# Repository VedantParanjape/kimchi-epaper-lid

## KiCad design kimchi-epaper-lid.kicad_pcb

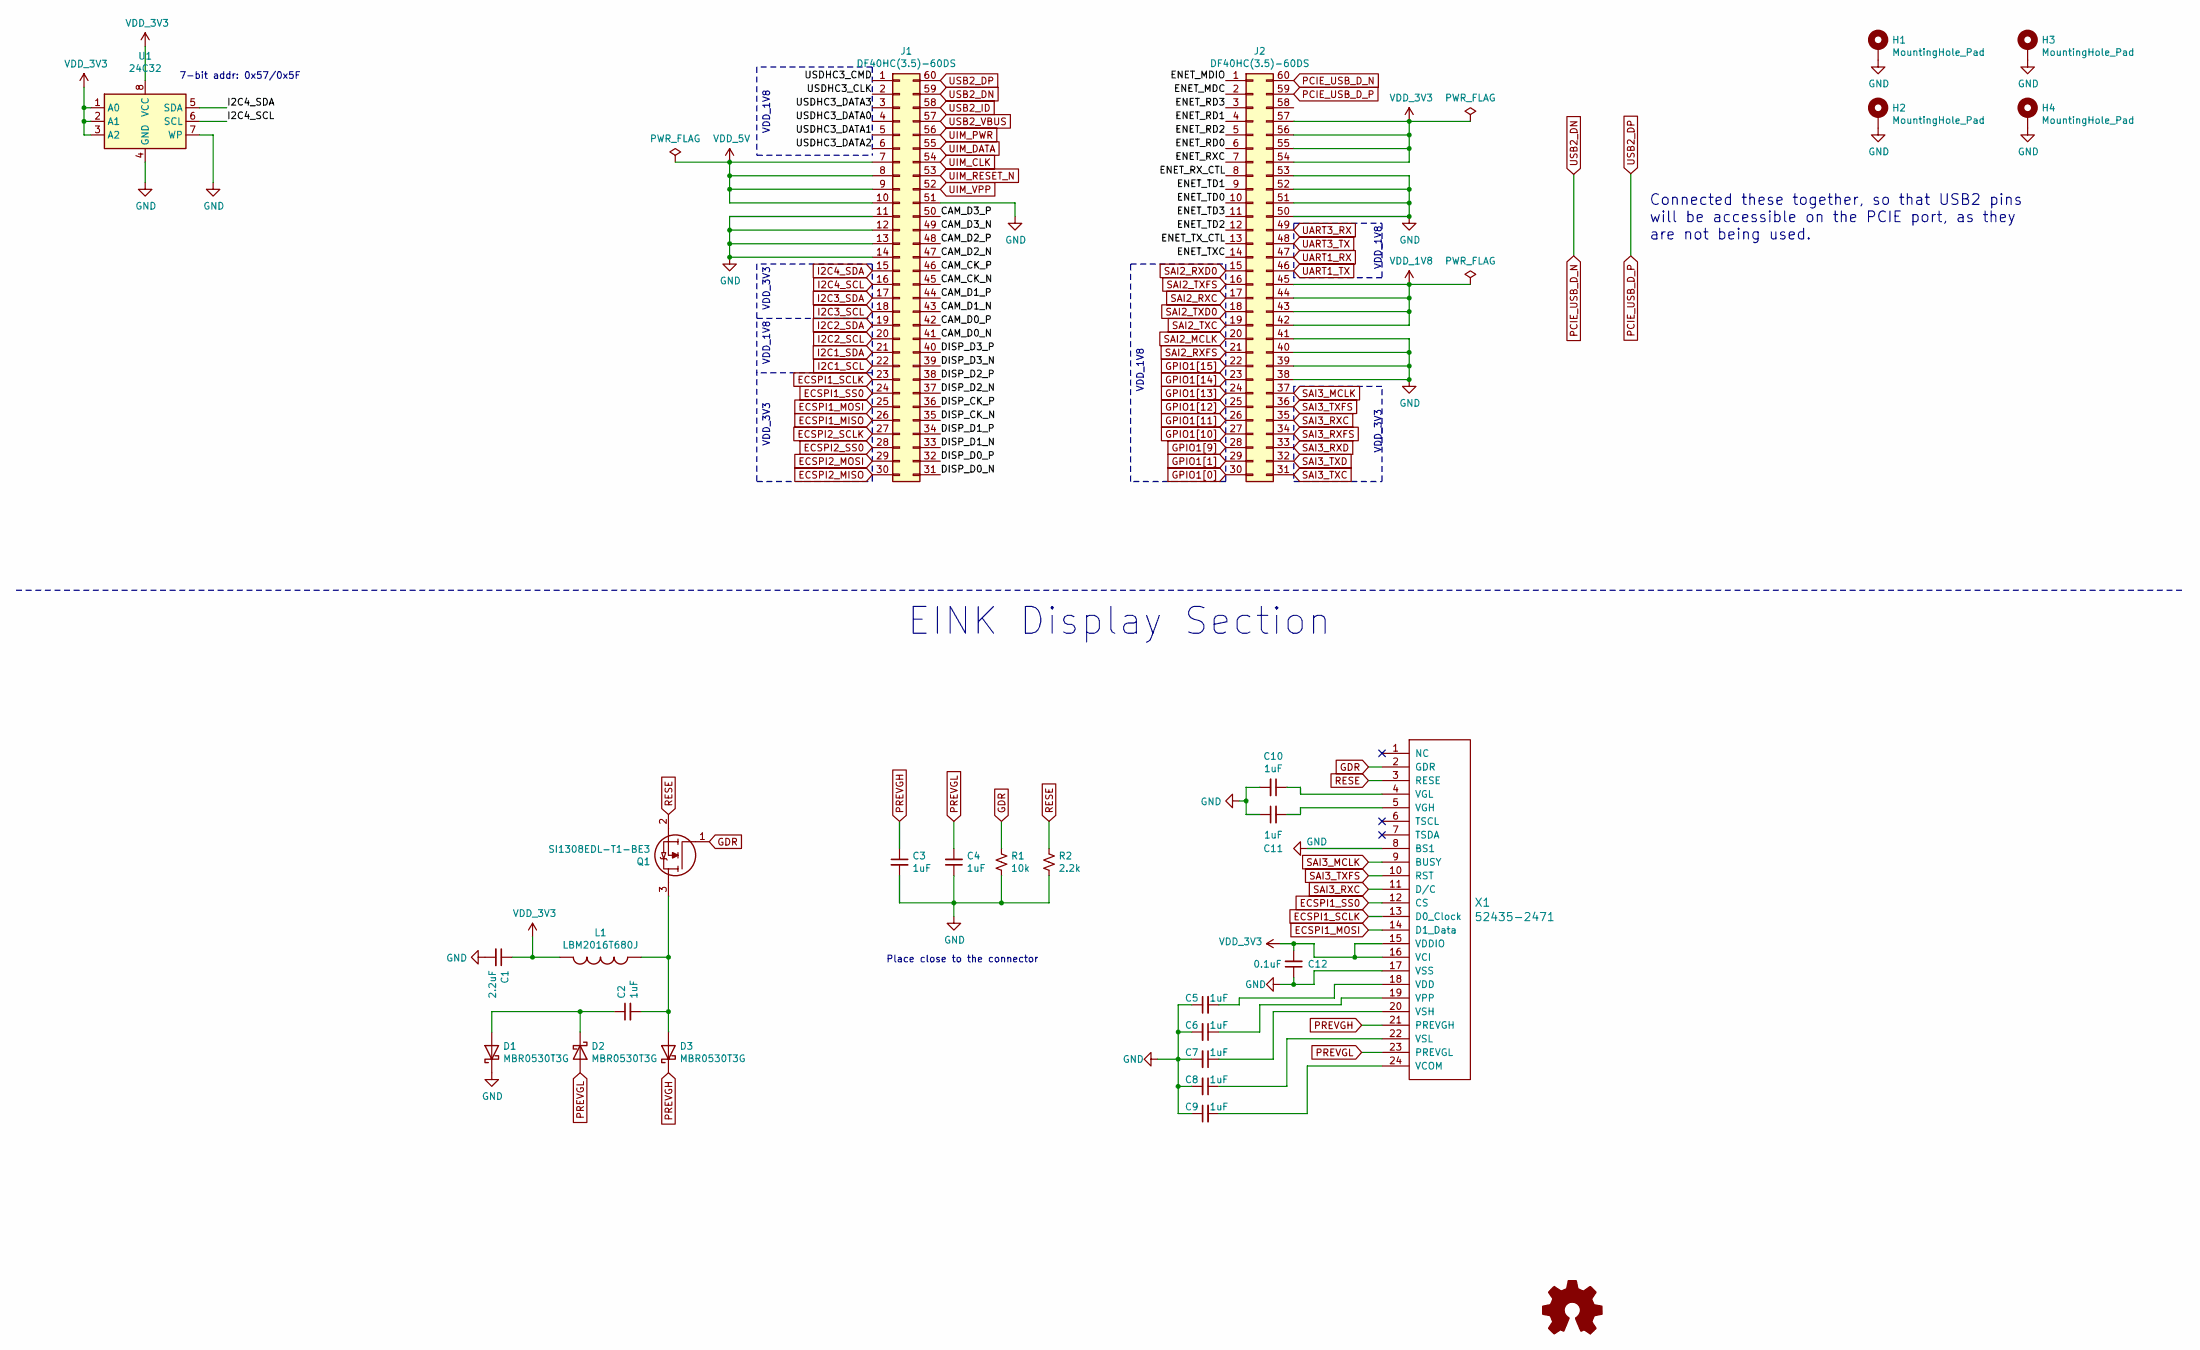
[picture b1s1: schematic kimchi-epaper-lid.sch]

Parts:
C1: 2.2uF; C_0603_1608Metric
C2, C3, C4, C5, C6, C7, C8, C9, C10, C11: 1uF; C_0603_1608Metric
C12: 0.1uF; C_0603_1608Metric
D1, D2, D3: MBR0530T3G; D_SOD-123
H1, H2, H3, H4: MountingHole_Pad; MountingHole_3mm_Pad
J1, J2: DF40HC(3.5)-60DS
L1: LBM2016T680J; INDC2016X180N
LOGO1: Logo_Open_Hardware_Small; OSHW-Logo_5.7x6mm_SilkScreen
Q1: SI1308EDL-T1-BE3; SOT65P210X110-3N; Manufacturer_Part_Number SI1308EDL-T1-BE3; Mouser Part Number 78-SI1308EDL-T1-BE3
R1: 10k; R_0603_1608Metric
R2: 2.2k; R_0603_1608Metric
U1: 24C32; DFN-8-1EP_3x2mm_P0.5mm_EP1.36x1.46mm; Part M24C32-FMC6TG
X1: 52435-2471; MOLEX_52435-2471

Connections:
/CAM_CK_N: J1.45
/CAM_CK_P: J1.46
/CAM_D0_N: J1.41
/CAM_D0_P: J1.42
/CAM_D1_N: J1.43
/CAM_D1_P: J1.44
/CAM_D2_N: J1.47
/CAM_D2_P: J1.48
/CAM_D3_N: J1.49
/CAM_D3_P: J1.50
/DISP_CK_N: J1.35
/DISP_CK_P: J1.36
/DISP_D0_N: J1.31
/DISP_D0_P: J1.32
/DISP_D1_N: J1.33
/DISP_D1_P: J1.34
/DISP_D2_N: J1.37
/DISP_D2_P: J1.38
/DISP_D3_N: J1.39
/DISP_D3_P: J1.40
/ENET_MDC: J2.2
/ENET_MDIO: J2.1
/ENET_RD0: J2.6
/ENET_RD1: J2.4
/ENET_RD2: J2.5
/ENET_RD3: J2.3
/ENET_RXC: J2.7
/ENET_RX_CTL: J2.8
/ENET_TD0: J2.10
/ENET_TD1: J2.9
/ENET_TD2: J2.12
/ENET_TD3: J2.11
/ENET_TXC: J2.14
/ENET_TX_CTL: J2.13
/USDHC3_CLK: J1.2
/USDHC3_CMD: J1.1
/USDHC3_DATA0: J1.4
/USDHC3_DATA1: J1.5
/USDHC3_DATA2: J1.6
/USDHC3_DATA3: J1.3
ECSPI1_MISO: J1.26
ECSPI1_MOSI: J1.25, X1.14 (D1_Data)
ECSPI1_SCLK: J1.23, X1.13 (D0_Clock)
ECSPI1_SS0: J1.24, X1.12 (CS)
ECSPI2_MISO: J1.30
ECSPI2_MOSI: J1.29
ECSPI2_SCLK: J1.27
ECSPI2_SS0: J1.28
GDR: Q1.1, R1.1, X1.2 (GDR)
GND: C1.2, C3.2, C4.1, C5.1, C6.2, C7.2, C8.2, C9.1, C10.2, C11.1, C12.1, D1.1 (K), H1.1, H2.1, H3.1, H4.1, J1.11, J1.12, J1.13, J1.14, J1.51, J2.38, J2.39, J2.40, J2.41, J2.50, J2.51, J2.52, J2.53, R1.2, R2.2, U1.4 (GND), U1.7 (WP), X1.8 (BS1), X1.17 (VSS)
GPIO1[0]: J2.30
GPIO1[1]: J2.29
GPIO1[9]: J2.28
GPIO1[10]: J2.27
GPIO1[11]: J2.26
GPIO1[12]: J2.25
GPIO1[13]: J2.24
GPIO1[14]: J2.23
GPIO1[15]: J2.22
I2C1_SCL: J1.22
I2C1_SDA: J1.21
I2C2_SCL: J1.20
I2C2_SDA: J1.19
I2C3_SCL: J1.18
I2C3_SDA: J1.17
I2C4_SCL: J1.16, U1.6 (SCL)
I2C4_SDA: J1.15, U1.5 (SDA)
unnamed: C2.1, D1.2 (A), D2.1 (K)
unnamed: C2.2, D3.2 (A), L1.2, Q1.3
unnamed: C5.2, X1.18 (VDD)
unnamed: C6.1, X1.19 (VPP)
unnamed: C7.1, X1.20 (VSH)
unnamed: C8.1, X1.22 (VSL)
unnamed: C9.2, X1.24 (VCOM)
unnamed: C10.1, X1.4 (VGL)
unnamed: C11.2, X1.5 (VGH)
PCIE_USB_D_N: J1.59, J2.60
PCIE_USB_D_P: J1.60, J2.59
PREVGH: C3.1, D3.1 (K), X1.21 (PREVGH)
PREVGL: C4.2, D2.2 (A), X1.23 (PREVGL)
RESE: Q1.2, R2.1, X1.3 (RESE)
SAI2_MCLK: J2.20
SAI2_RXC: J2.17
SAI2_RXD0: J2.15
SAI2_RXFS: J2.21
SAI2_TXC: J2.19
SAI2_TXD0: J2.18
SAI2_TXFS: J2.16
SAI3_MCLK: J2.37, X1.9 (BUSY)
SAI3_RXC: J2.35, X1.11 (D/C)
SAI3_RXD: J2.33
SAI3_RXFS: J2.34
SAI3_TXC: J2.31
SAI3_TXD: J2.32
SAI3_TXFS: J2.36, X1.10 (RST)
UART1_RX: J2.47
UART1_TX: J2.46
UART3_RX: J2.49
UART3_TX: J2.48
UIM_CLK: J1.54
UIM_DATA: J1.55
UIM_PWR: J1.56
UIM_RESET_N: J1.53
UIM_VPP: J1.52
USB2_ID: J1.58
USB2_VBUS: J1.57
VDD_1V8: J2.42, J2.43, J2.44, J2.45
VDD_3V3: C1.1, C12.2, J2.54, J2.55, J2.56, J2.57, L1.1, U1.1 (A0), U1.2 (A1), U1.3 (A2), U1.8 (VCC), X1.15 (VDDIO), X1.16 (VCI)
VDD_5V: J1.7, J1.8, J1.9, J1.10

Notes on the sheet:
7-bit addr: 0x57/0x5F
VDD_1V8
VDD_3V3
EINK Display Section
Place close to the connector
Connected these together, so that USB2 pins will be accessible on the PCIE port, as they are not being used.

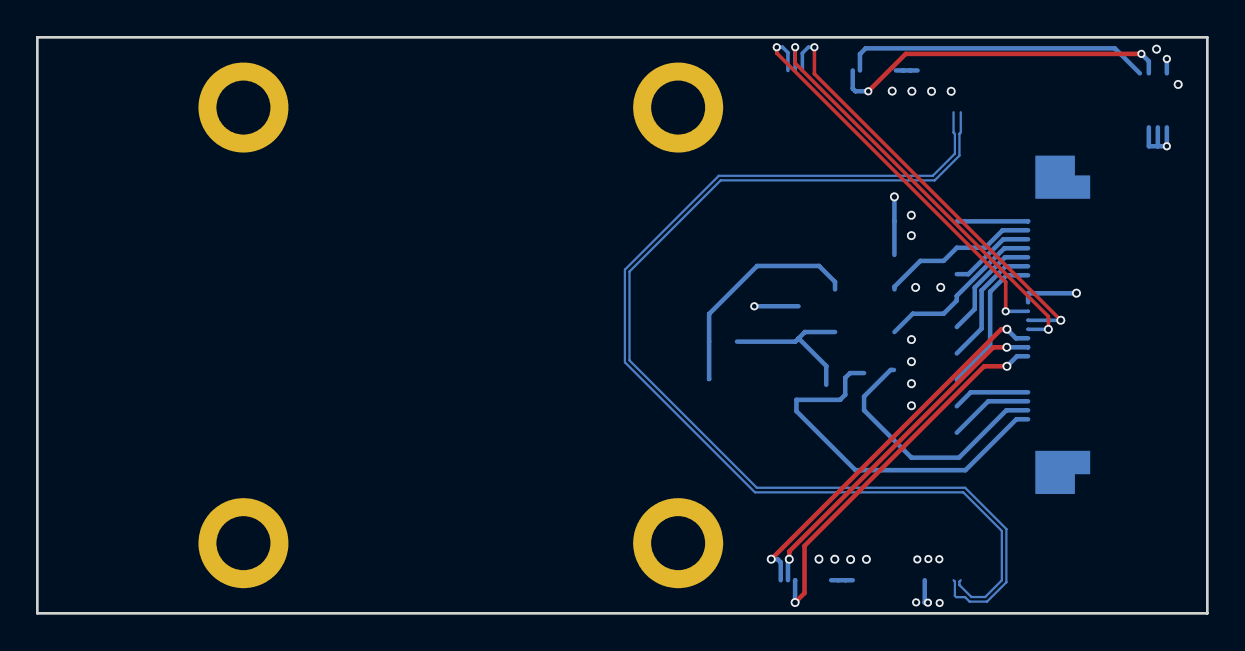
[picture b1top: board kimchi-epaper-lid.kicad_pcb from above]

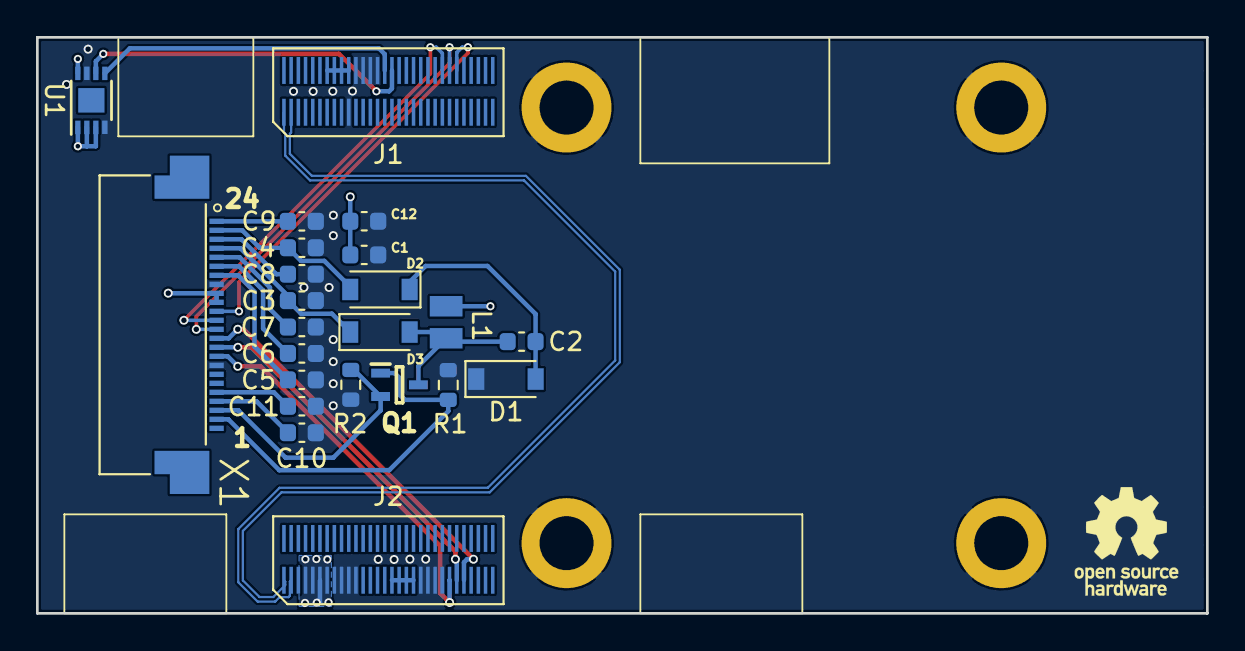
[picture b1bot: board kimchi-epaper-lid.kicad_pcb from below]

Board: 4 copper layers, 65.0 x 32.0 mm, 28 parts (24 on the bottom side), 27 nets.

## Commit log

2021-02-12 Partially completed schematics of the lid
2021-03-09 prouting a few components and updated position
2021-03-15 Completed routing
2021-03-21 Updated routing
2021-03-22 Fixed issues with routing
2021-03-22 Added 3d model of fpc connector
2021-04-06 Replaced inductor and completed routing (acq review)
2021-07-12 Fixed mistake in mosfet schematics

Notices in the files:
kimchi-epaper-lid.sch:
License: MIT LICENSE
